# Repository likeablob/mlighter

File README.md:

# MLIGHTER
[An optically re-writable](https://mlighter.now.sh/) tiny LED badge.

## Project structure
- [`pio/`](./pio) - Source code of the firmware(PlatformIO)
- [`kicad/`](./kicad) - PCB design (KiCad)
- [`openscad/`](./openscad) - Models for the 3D-printable jig. (OpenSCAD)
- https://github.com/likeablob/mlighter-webui - Source code of the Web UI(Nuxt.js + Vuetify)

## Build Instructions
WIP

## BOM
| Name               | Description      | Amount | Price   |
| ------------------ | ---------------- | ------ | ------- |
| ATiny85 (SOIC)     | uC               | 1      | ~1 USD  |
| MAX7219            | LED Driver       | 1      | 0.2 USD |
| SFH3710            | Photo Transistor | 1      | 0.2 USD |
| 8x8 LED Dot Matrix | (32x32mm)        | 1      | ~1 USD  |
| CR2032             | Coin Cell        | 1      | -       |

## Refs
WIP

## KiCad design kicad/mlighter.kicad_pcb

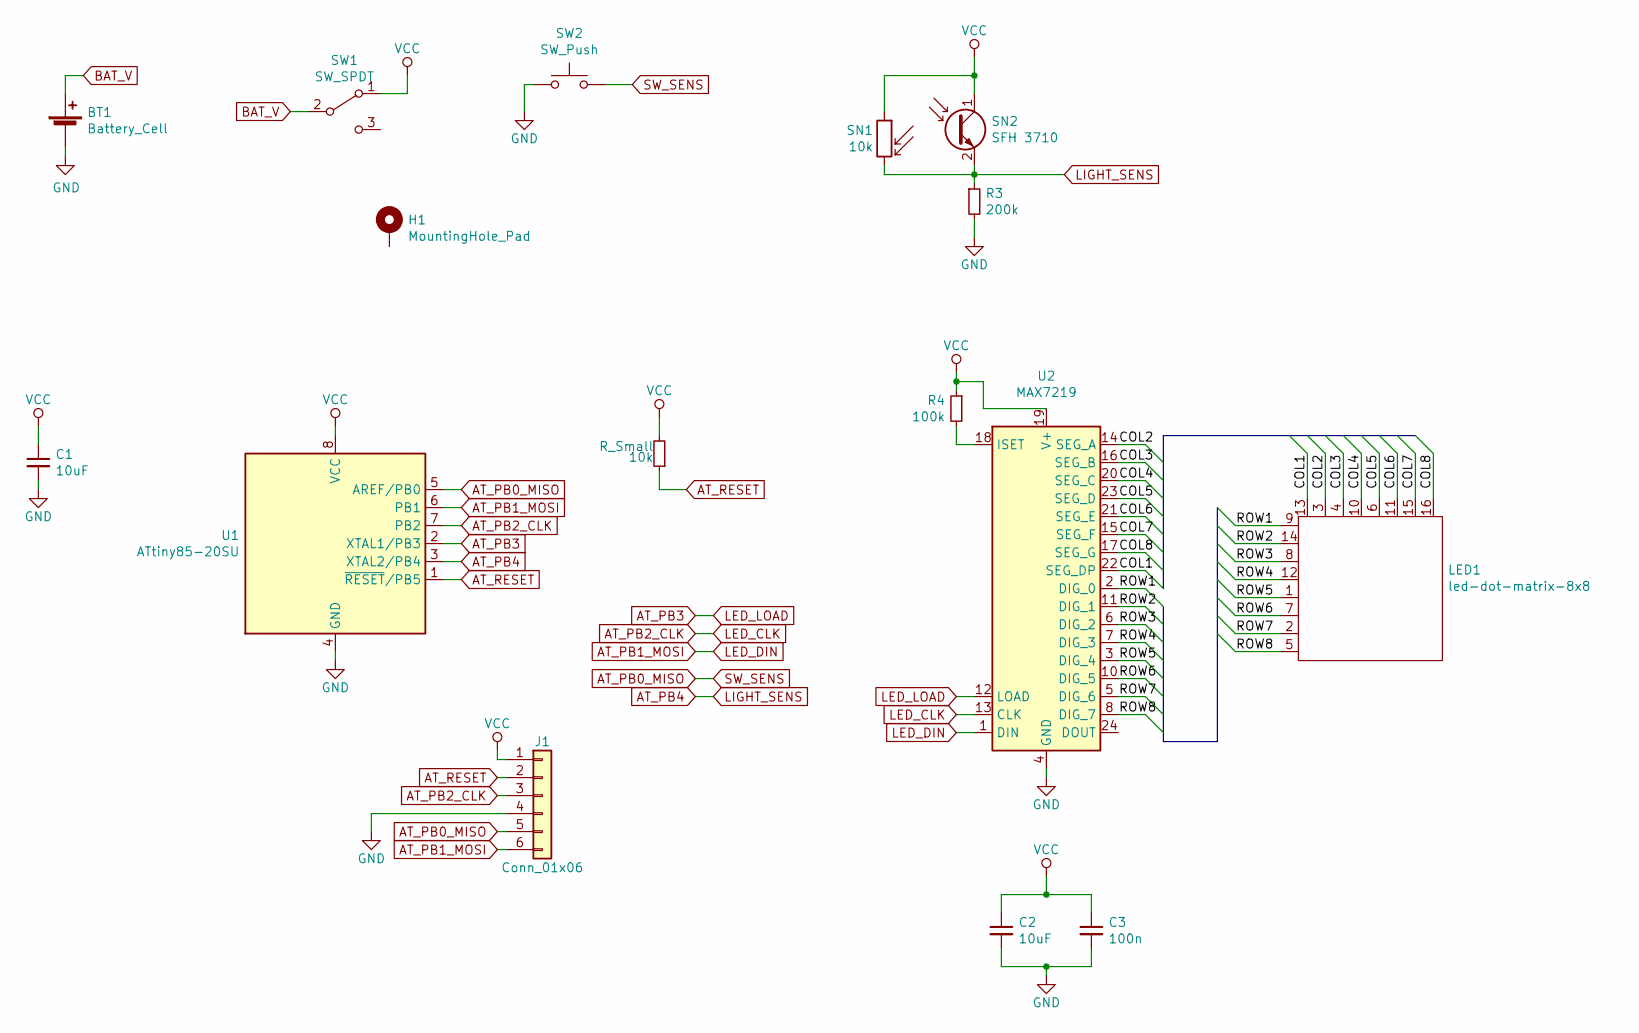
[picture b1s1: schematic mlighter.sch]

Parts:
10k: R_Small; R_0805_2012Metric
BT1: Battery_Cell; BatteryHolder_Keystone_1060_1x2032_short
C1, C2: 10uF; C_0805_2012Metric_Pad1.15x1.40mm_HandSolder
C3: 100n; C_0805_2012Metric_Pad1.15x1.40mm_HandSolder
H1: MountingHole_Pad; brooch-pin-15mm
J1: Conn_01x06; PinHeader_1x06_P2.54mm_Vertical
LED1: led-dot-matrix-8x8
R3: 200k; R_0805_2012Metric
R4: 100k; R_0805_2012Metric
SN1: 10k; R_Axial_DIN0204_L3.6mm_D1.6mm_P2.54mm_Vertical
SN2: SFH 3710; LED_0805_2012Metric
SW1: SW_SPDT; MSK12C02
SW2: SW_Push; SW_Push_1P1T_NO_CK_KMR2
U1: ATtiny85-20SU; SOIJ-8_5.3x5.3mm_P1.27mm
U2: MAX7219; SOP-24_7.5x15.4mm_P1.27mm

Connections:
/COL1: LED1.13, U2.22 (SEG_DP)
/COL2: LED1.3, U2.14 (SEG_A)
/COL3: LED1.4, U2.16 (SEG_B)
/COL4: LED1.10, U2.20 (SEG_C)
/COL5: LED1.6, U2.23 (SEG_D)
/COL6: LED1.11, U2.21 (SEG_E)
/COL7: LED1.15, U2.15 (SEG_F)
/COL8: LED1.16, U2.17 (SEG_G)
/ROW1: LED1.9, U2.2 (DIG_0)
/ROW2: LED1.14, U2.11 (DIG_1)
/ROW3: LED1.8, U2.6 (DIG_2)
/ROW4: LED1.12, U2.7 (DIG_3)
/ROW5: LED1.1, U2.3 (DIG_4)
/ROW6: LED1.7, U2.10 (DIG_5)
/ROW7: LED1.2, U2.5 (DIG_6)
/ROW8: LED1.5, U2.8 (DIG_7)
AT_PB0_MISO: J1.5, SW2.2, U1.5 (AREF/PB0)
AT_PB1_MOSI: J1.6, U1.6 (PB1), U2.1 (DIN)
AT_PB2_CLK: J1.3, U1.7 (PB2), U2.13 (CLK)
AT_PB3: U1.2 (XTAL1/PB3), U2.12 (LOAD)
AT_PB4: R3.1, SN1.2, SN2.2 (E), U1.3 (XTAL2/PB4)
AT_RESET: 10k.1, J1.2, U1.1 (~RESET~/PB5); also elsewhere on the board
BAT_V: BT1.1 (+), SW1.2 (B)
GND: BT1.2 (-), C1.2, C2.2, C3.2, J1.4, R3.2, SW2.1, U1.4 (GND), U2.4 (GND), U2.9 (GND)
unnamed: R4.2, U2.18 (ISET)
VCC: 10k.2, C1.1, C2.1, C3.1, J1.1, R4.1, SN1.1, SN2.1 (C), SW1.1 (A), U1.8 (VCC), U2.19 (V+); also elsewhere on the board

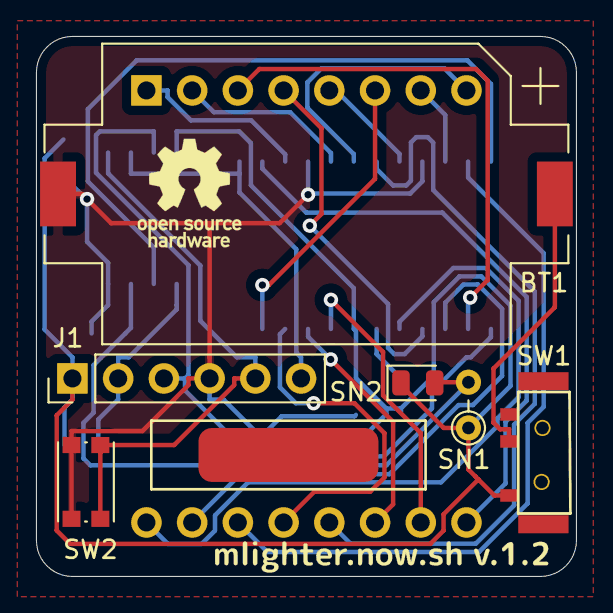
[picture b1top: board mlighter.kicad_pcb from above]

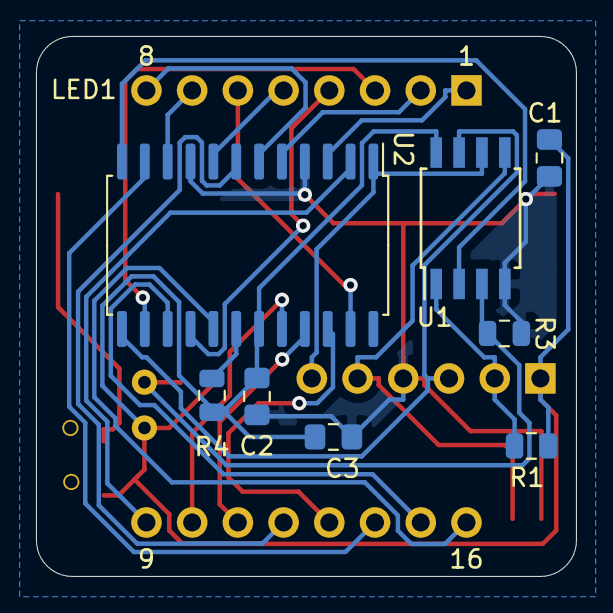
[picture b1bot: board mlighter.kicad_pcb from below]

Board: 2 copper layers, 30.0 x 30.0 mm, 16 parts (9 on the bottom side), 26 nets.

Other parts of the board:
R1: R_Small; R_0805_2012Metric

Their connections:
AT_RESET: R1.1; also elsewhere on the board
VCC: R1.2; also elsewhere on the board

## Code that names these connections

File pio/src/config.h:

#pragma once

#define PIN_SW0 PB0
#define PIN_SENS PB4

#define PIN_LED_DATA PB1
#define PIN_LED_CLK PB2
#define PIN_LED_CS PB3

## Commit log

2019-12-14 Add files
